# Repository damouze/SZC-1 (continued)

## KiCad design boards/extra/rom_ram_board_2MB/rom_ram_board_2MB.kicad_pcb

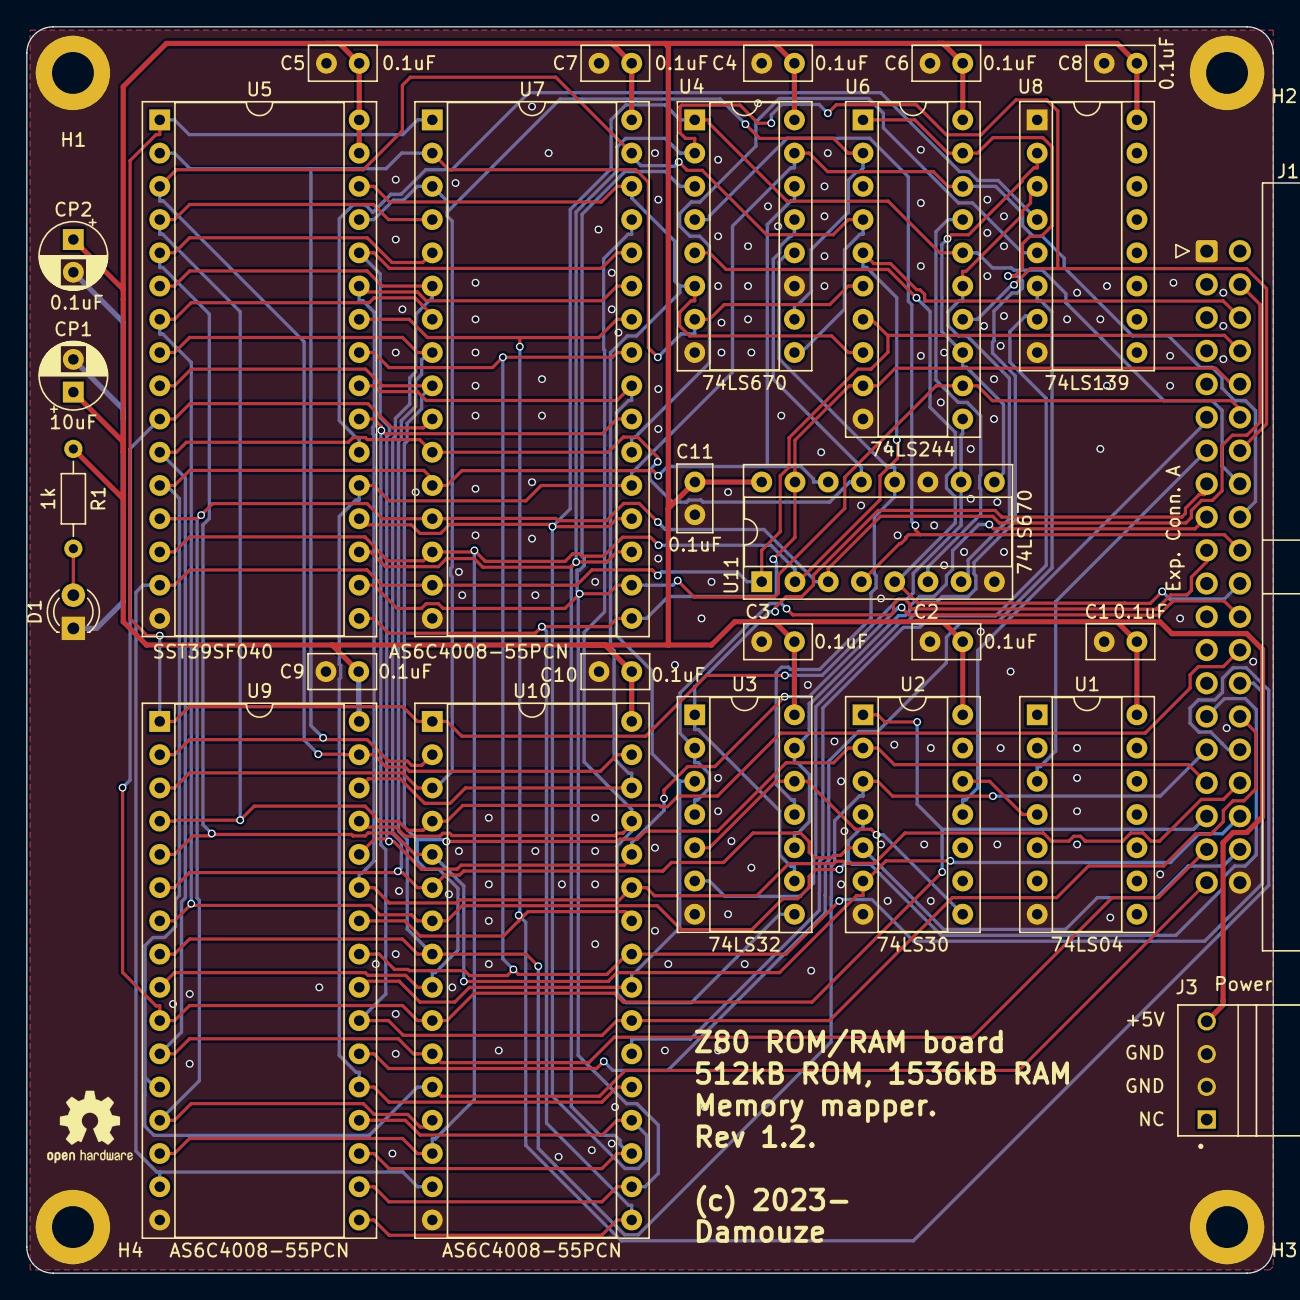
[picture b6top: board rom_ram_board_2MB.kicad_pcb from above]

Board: 2 copper layers, 95.2 x 95.2 mm, 32 parts (0 on the bottom side), 50 nets.

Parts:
C1, C2, C3, C4, C5, C6, C7, C8, C9, C10, C11: 0.1uF; C_Disc_D5.0mm_W2.5mm_P2.50mm
CP1: 10uF; CP_Radial_D5.0mm_P2.50mm
CP2: 0.1uF; CP_Radial_D5.0mm_P2.50mm
D1: PWR_LED; LED_D3.0mm
H1, H2, H3, H4: MountingHole_Pad; MountingHole_3.2mm_M3_ISO7380_Pad
J1: Exp. Conn. A; IDC-Header_2x20_P2.54mm_Horizontal
J3: Power; TE_171826-4
R1: 1k; R_Axial_DIN0204_L3.6mm_D1.6mm_P7.62mm_Horizontal
U1: 74LS04; DIP-14_W7.62mm_Socket
U2: 74LS30; DIP-14_W7.62mm_Socket
U3: 74LS32; DIP-14_W7.62mm_Socket
U4, U11: 74LS670; DIP-16_W7.62mm_Socket
U5: SST39SF040; DIP-32_W15.24mm_Socket
U6: 74LS244; DIP-20_W7.62mm_Socket
U7, U9, U10: AS6C4008-55PCN; DIP-32_W15.24mm_Socket
U8: 74LS139; DIP-16_W7.62mm_Socket

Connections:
/+5V: C1.1, C2.1, C3.1, C4.1, C5.1, C6.1, C7.1, C8.1, C9.1, C10.1, C11.1, CP1.1, CP2.1, J3.4, R1.1, U1.14 (VCC), U2.14 (VCC), U3.14 (VCC), U4.16 (VCC), U5.31 (PGM), U5.32 (VCC), U6.20 (VCC), U7.32 (VCC), U8.16 (VCC), U9.32 (VCC), U10.32 (VCC), U11.16 (VCC)
/B_A0: J1.39, U4.14 (Wa), U5.12 (A0), U7.12 (A0), U9.12 (A0), U10.12 (A0), U11.14 (Wa)
/B_A1: J1.37, U4.13 (Wb), U5.11 (A1), U7.11 (A1), U9.11 (A1), U10.11 (A1), U11.13 (Wb)
/B_A2: J1.35, U2.1, U5.10 (A2), U7.10 (A2), U9.10 (A2), U10.10 (A2)
/B_A3: J1.33, U2.2, U5.9 (A3), U7.9 (A3), U9.9 (A3), U10.9 (A3)
/B_A4: J1.31, U2.3, U5.8 (A4), U7.8 (A4), U9.8 (A4), U10.8 (A4)
/B_A5: J1.29, U2.4, U5.7 (A5), U7.7 (A5), U9.7 (A5), U10.7 (A5)
/B_A6: J1.38, U2.5, U5.6 (A6), U7.6 (A6), U9.6 (A6), U10.6 (A6)
/B_A7: J1.36, U2.6, U5.5 (A7), U7.5 (A7), U9.5 (A7), U10.5 (A7)
/B_A8: J1.34, U5.27 (A8), U7.27 (A8), U9.27 (A8), U10.27 (A8)
/B_A9: J1.32, U5.26 (A9), U7.26 (A9), U9.26 (A9), U10.26 (A9)
/B_A10: J1.30, U5.23 (A10), U7.23 (A10), U9.23 (A10), U10.23 (A10)
/B_A11: J1.28, U5.25 (A11), U7.25 (A11), U9.25 (A11), U10.25 (A11)
/B_A12: J1.26, U5.4 (A12), U7.4 (A12), U9.4 (A12), U10.4 (A12)
/B_A13: J1.24, U5.28 (A13), U7.28 (A13), U9.28 (A13), U10.28 (A13)
/B_A14: J1.22, U4.5 (Ra), U11.5 (Ra)
/B_A15: J1.20, U4.4 (Rb), U11.4 (Rb)
/B_D0: J1.18, U4.15 (D1), U5.21 (D7), U6.18 (O0a), U7.21 (DQ7), U9.21 (DQ7), U10.21 (DQ7)
/B_D1: J1.16, U4.1 (D2), U5.20 (D6), U6.16 (O1a), U7.20 (DQ6), U9.20 (DQ6), U10.20 (DQ6)
/B_D2: J1.14, U4.2 (D3), U5.19 (D5), U6.14 (O2a), U7.19 (DQ5), U9.19 (DQ5), U10.19 (DQ5)
/B_D3: J1.12, U4.3 (D4), U5.18 (D4), U6.12 (O3a), U7.18 (DQ4), U9.18 (DQ4), U10.18 (DQ4)
/B_D4: J1.10, U5.17 (D3), U6.9 (O0b), U7.17 (DQ3), U9.17 (DQ3), U10.17 (DQ3), U11.15 (D1)
/B_D5: J1.8, U5.15 (D2), U6.7 (O1b), U7.15 (DQ2), U9.15 (DQ2), U10.15 (DQ2), U11.1 (D2)
/B_D6: J1.6, U5.14 (D1), U6.5 (O2b), U7.14 (DQ1), U9.14 (DQ1), U10.14 (DQ1), U11.2 (D3)
/B_D7: J1.4, U5.13 (D0), U7.13 (DQ0), U9.13 (DQ0), U10.13 (DQ0), U11.3 (D4)
/GND: C1.2, C2.2, C3.2, C4.2, C5.2, C6.2, C7.2, C8.2, C9.2, C10.2, C11.2, CP1.2, CP2.2, D1.1 (K), H1.1, H2.1, H3.1, H4.1, J1.1, J1.40, J3.2, J3.3, U1.7 (GND), U2.7 (GND), U3.7 (GND), U4.8 (GND), U4.11 (~Er), U5.16 (GND), U6.10 (GND), U7.16 (VSS), U8.1 (E), U8.8 (GND), U9.16 (VSS), U10.16 (VSS), U11.8 (GND), U11.11 (~Er)
/IORQ: U1.4, U2.12
/R_A14: U4.10 (Q1), U5.29 (A14), U6.2 (I0a), U7.3 (A14), U9.3 (A14), U10.3 (A14)
/R_A15: U4.9 (Q2), U5.3 (A15), U6.4 (I1a), U7.31 (A15), U9.31 (A15), U10.31 (A15)
/R_A16: U4.7 (Q3), U5.2 (A16), U6.6 (I2a), U7.2 (A16), U9.2 (A16), U10.2 (A16)
/R_A17: U4.6 (Q4), U5.30 (A17), U6.8 (I3a), U7.30 (A17), U9.30 (A17), U10.30 (A17)
/R_A18: U5.1 (A18), U6.11 (I0b), U7.1 (A18), U9.1 (A18), U10.1 (A18), U11.10 (Q1)
/R_A19: U6.13 (I1b), U8.2 (A0), U11.9 (Q2)
/R_A20: U6.15 (I2b), U8.3 (A1), U11.7 (Q3)
/R_A21: U6.17 (I3b), U11.6 (Q4)
/~B_IORQ: J1.13, U1.3
/~B_M1: J1.11, U2.11
/~B_MREQ: J1.15, U3.1, U3.9
/~B_RD: J1.19, U3.2, U3.4
/~B_WR: J1.17, U3.10, U3.13
/~IO_RD: U3.6, U6.1 (OEa), U6.19 (OEb)
/~IO_WR: U3.11, U4.12 (~Ew), U11.12 (~Ew)
/~MM_RD: U3.3, U5.24 (OE), U7.24 (OE#), U9.24 (OE#), U10.24 (OE#)
/~MM_WR: U3.8, U7.29 (WE#), U9.29 (WE#), U10.29 (WE#)
/~RAM1_CS: U7.22 (CE#), U8.5 (O1)
/~RAM2_CS: U8.6 (O2), U9.22 (CE#)
/~RAM3_CS: U8.7 (O3), U10.22 (CE#)
/~ROM_CS: U5.22 (CE), U8.4 (O0)
unnamed: D1.2 (A), R1.2
unnamed: U2.8, U3.5, U3.12

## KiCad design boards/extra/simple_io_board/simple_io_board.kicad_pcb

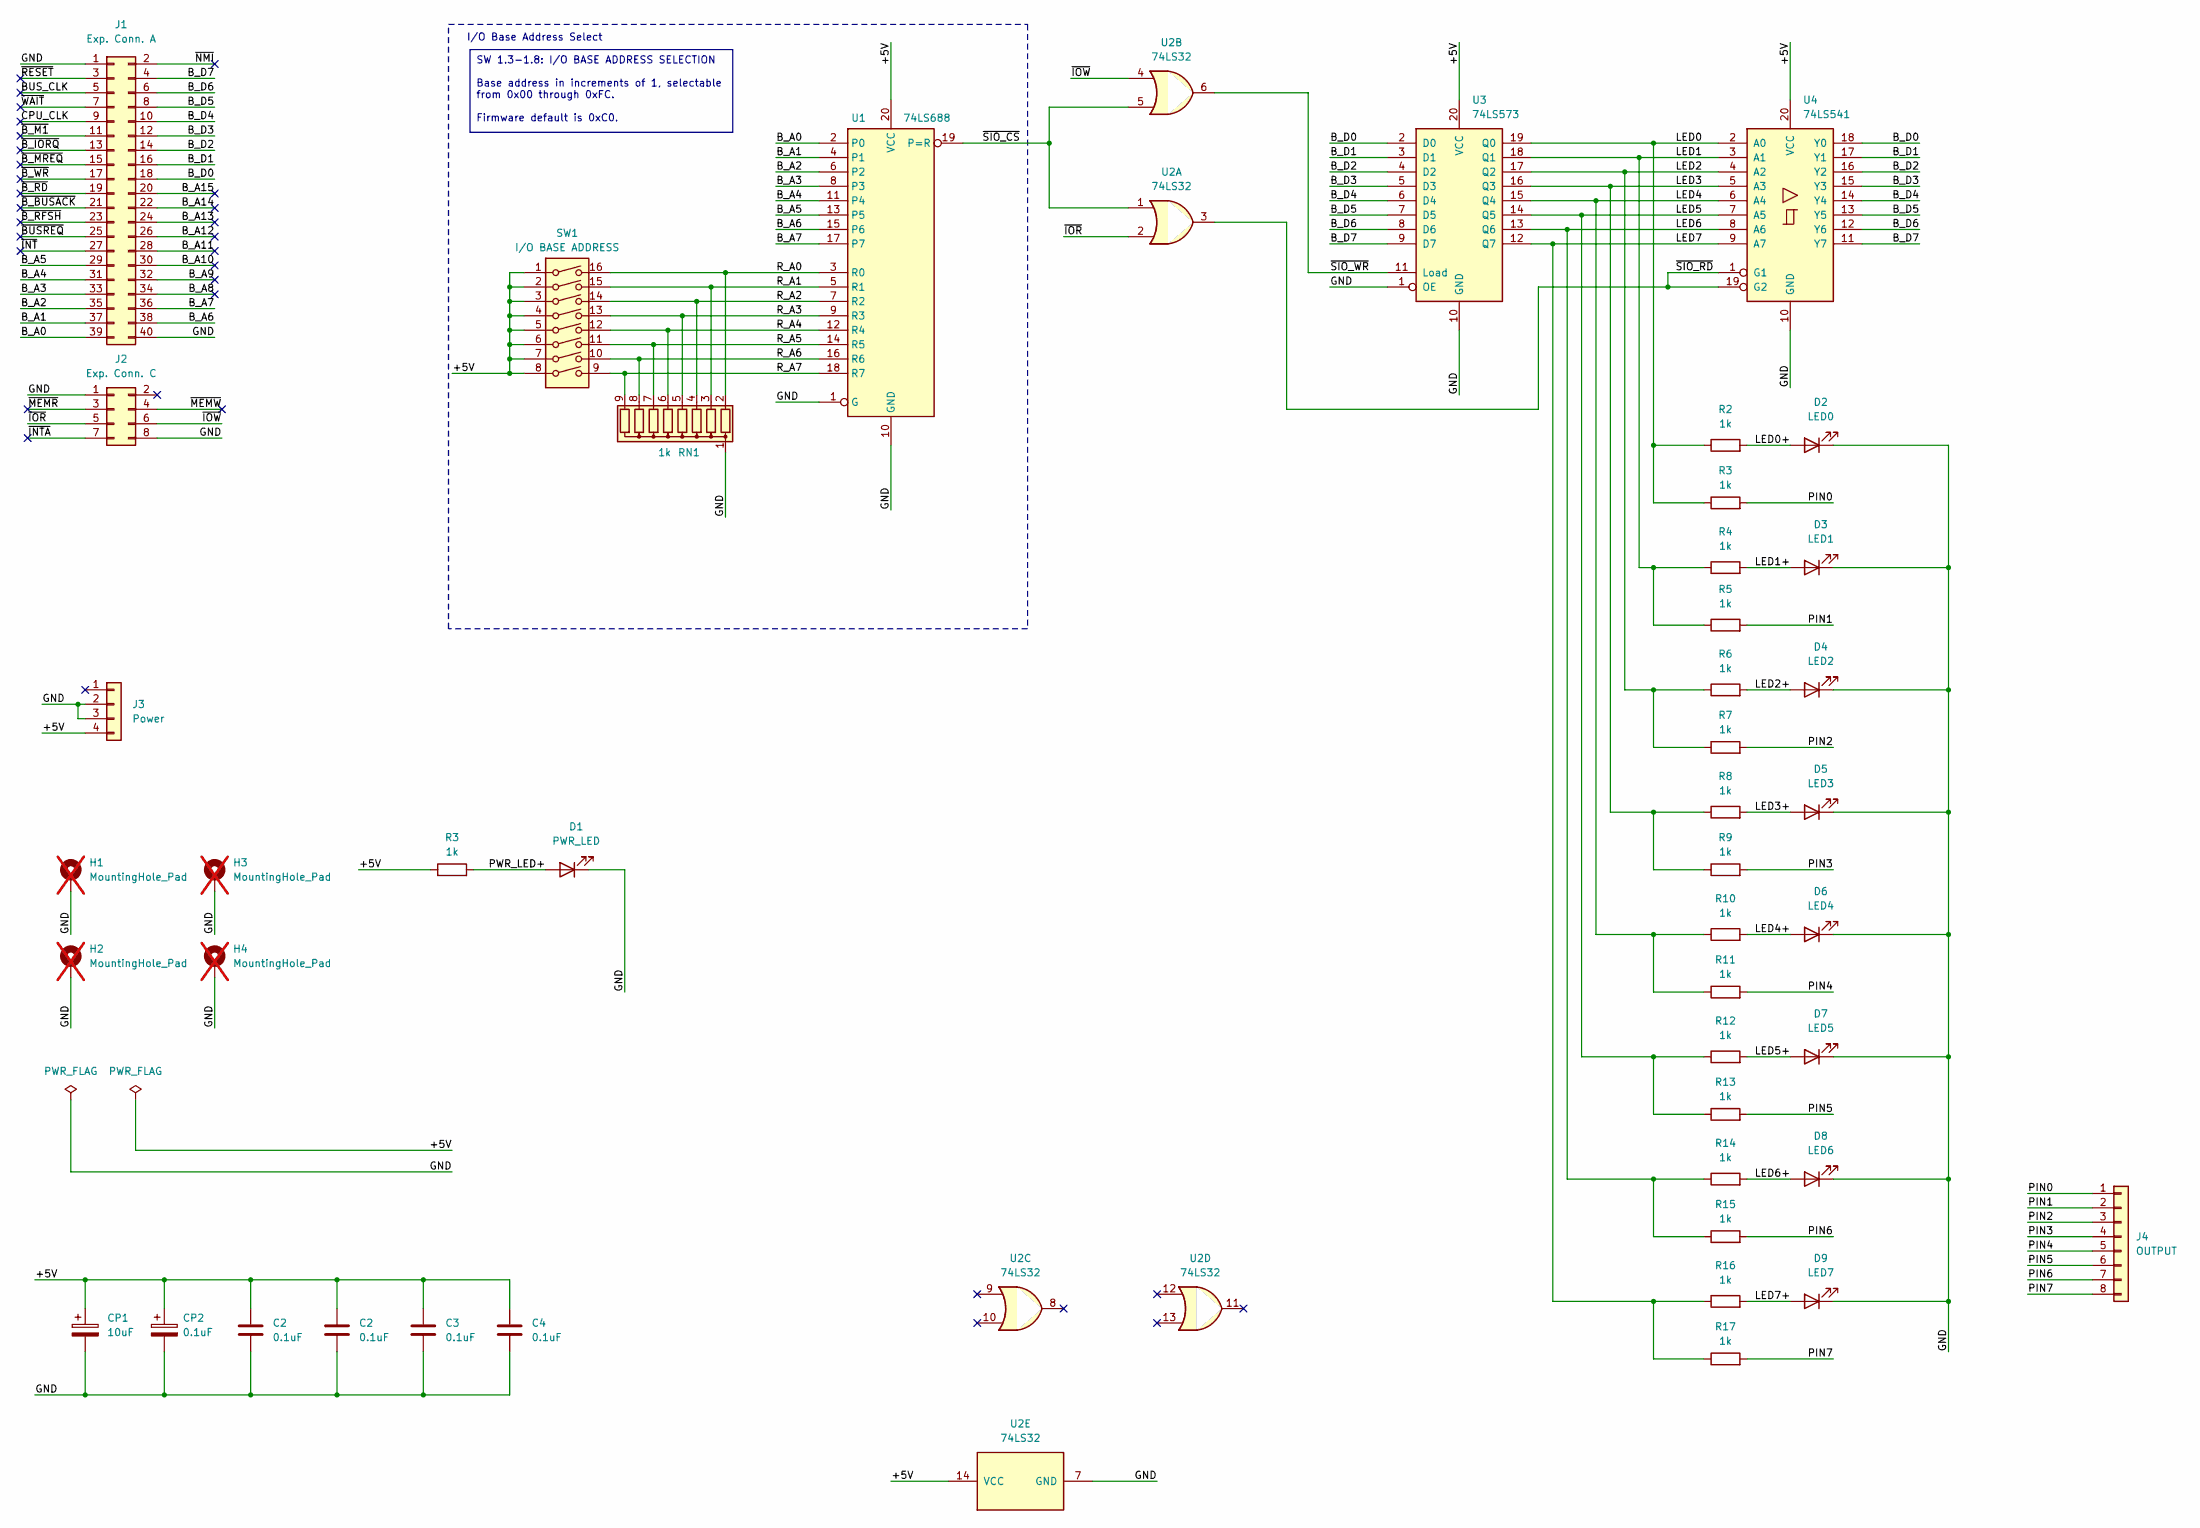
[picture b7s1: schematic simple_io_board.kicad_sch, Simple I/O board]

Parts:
C2, C3, C4: 0.1uF; C_Disc_D5.0mm_W2.5mm_P2.50mm; MPN FG28X7R1H104KNT06
CP1: 10uF; CP_Radial_D5.0mm_P2.50mm; MPN ECA1HM100I
CP2: 0.1uF; CP_Radial_D5.0mm_P2.50mm; MPN KS104M050C07RR0VH2FP0
D1: PWR_LED; LED_D3.0mm; MPN HLMP-1700
D2: LED0; LED_D3.0mm; MPN HLMP-1700
D3: LED1; LED_D3.0mm; MPN HLMP-1700
D4: LED2; LED_D3.0mm; MPN HLMP-1700
D5: LED3; LED_D3.0mm; MPN HLMP-1700
D6: LED4; LED_D3.0mm; MPN HLMP-1700
D7: LED5; LED_D3.0mm; MPN HLMP-1700
D8: LED6; LED_D3.0mm; MPN HLMP-1700
D9: LED7; LED_D3.0mm; MPN HLMP-1700
H1, H2, H3, H4: MountingHole_Pad; MountingHole_3.2mm_M3_ISO7380_Pad; not fitted
J1: Exp. Conn. A; IDC-Header_2x20_P2.54mm_Horizontal; MPN X9555WR-2x20-6TV01
J2: Exp. Conn. C; IDC-Header_2x04_P2.54mm_Horizontal; MPN 75867-132LF
J3: Power; TE_171826-4; MPN 171826-4
J4: OUTPUT; PinHeader_1x08_P2.54mm_Horizontal; MPN PZ254R-11-08P
R2, R3, R4, R5, R6, R7, R8, R9, R10, R11, R12, R13, R14, R15, R16, R17: 1k; R_Axial_DIN0204_L3.6mm_D1.6mm_P7.62mm_Horizontal; MPN MBA02040C1001FC100
RN1: 1k; R_Array_SIP9; MPN MBA02040C1001FC100
SW1: I/O BASE ADDRESS; SW_DIP_SPSTx08_Slide_6.7x21.88mm_W7.62mm_P2.54mm_LowProfile; MPN DS-08BLP
U1: 74LS688; DIP-20_W7.62mm_Socket; MPN 1-2199298-6
U2: 74LS32; DIP-14_W7.62mm_Socket; MPN 1-2199298-3
U3: 74LS573; DIP-20_W7.62mm_Socket; MPN 1-2199298-6
U4: 74LS541; DIP-20_W7.62mm_Socket; MPN 1-2199298-6

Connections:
/BUS_CLK: J1.5
/B_A0: J1.39, U1.2 (P0)
/B_A1: J1.37, U1.4 (P1)
/B_A2: J1.35, U1.6 (P2)
/B_A3: J1.33, U1.8 (P3)
/B_A4: J1.31, U1.11 (P4)
/B_A5: J1.29, U1.13 (P5)
/B_A6: J1.38, U1.15 (P6)
/B_A7: J1.36, U1.17 (P7)
/B_A8: J1.34
/B_A9: J1.32
/B_A10: J1.30
/B_A11: J1.28
/B_A12: J1.26
/B_A13: J1.24
/B_A14: J1.22
/B_A15: J1.20
/B_D0: J1.18, U3.2 (D0), U4.18 (Y0)
/B_D1: J1.16, U3.3 (D1), U4.17 (Y1)
/B_D2: J1.14, U3.4 (D2), U4.16 (Y2)
/B_D3: J1.12, U3.5 (D3), U4.15 (Y3)
/B_D4: J1.10, U3.6 (D4), U4.14 (Y4)
/B_D5: J1.8, U3.7 (D5), U4.13 (Y5)
/B_D6: J1.6, U3.8 (D6), U4.12 (Y6)
/B_D7: J1.4, U3.9 (D7), U4.11 (Y7)
/CPU_CLK: J1.9
/GND: C2.2, C3.2, C4.2, CP1.2, CP2.2, D1.1 (K), D2.1 (K), D3.1 (K), D4.1 (K), D5.1 (K), D6.1 (K), D7.1 (K), D8.1 (K), D9.1 (K), H1.1, H2.1, H3.1, H4.1, J1.1, J1.40, J2.1, J2.8, J3.2, J3.3, RN1.1 (common), U1.1 (G), U1.10 (GND), U2.7 (GND), U3.1 (OE), U3.10 (GND), U4.10 (GND); also elsewhere on the board
/LED0+: D2.2 (A), R2.2
/LED1: R4.1, R5.1, U3.18 (Q1), U4.3 (A1)
/LED1+: D3.2 (A), R4.2
/LED2: R6.1, R7.1, U3.17 (Q2), U4.4 (A2)
/LED2+: D4.2 (A), R6.2
/LED3: R8.1, R9.1, U3.16 (Q3), U4.5 (A3)
/LED3+: D5.2 (A), R8.2
/LED4: R10.1, R11.1, U3.15 (Q4), U4.6 (A4)
/LED4+: D6.2 (A), R10.2
/LED5: R12.1, R13.1, U3.14 (Q5), U4.7 (A5)
/LED5+: D7.2 (A), R12.2
/LED6: R14.1, R15.1, U3.13 (Q6), U4.8 (A6)
/LED6+: D8.2 (A), R14.2
/LED7: R16.1, R17.1, U3.12 (Q7), U4.9 (A7)
/LED7+: D9.2 (A), R16.2
/PIN1: J4.2, R5.2
/PIN2: J4.3, R7.2
/PIN3: J4.4, R9.2
/PIN4: J4.5, R11.2
/PIN5: J4.6, R13.2
/PIN6: J4.7, R15.2
/PIN7: J4.8, R17.2
/R_A0: RN1.2 (R1), SW1.16, U1.3 (R0)
/R_A1: RN1.3 (R2), SW1.15, U1.5 (R1)
/R_A2: RN1.4 (R3), SW1.14, U1.7 (R2)
/R_A3: RN1.5 (R4), SW1.13, U1.9 (R3)
/R_A4: RN1.6 (R5), SW1.12, U1.12 (R4)
/R_A5: RN1.7 (R6), SW1.11, U1.14 (R5)
/R_A6: RN1.8 (R7), SW1.10, U1.16 (R6)
/R_A7: RN1.9 (R8), SW1.9, U1.18 (R7)
/~BUSREQ: J1.25
/~B_BUSACK: J1.21
/~B_IORQ: J1.13
/~B_M1: J1.11
/~B_MREQ: J1.15
/~B_RD: J1.19
/~B_RFSH: J1.23
/~B_WR: J1.17
/~INTA: J2.7
/~INT: J1.27
/~IOR: J2.5, U2.2
/~IOW: J2.6, U2.4
/~MEMR: J2.3
/~MEMW: J2.4
/~NMI: J1.2
/~RESET: J1.3
/~SIO_CS: U1.19 (P=R), U2.1, U2.5
/~SIO_RD: U2.3, U4.1 (G1), U4.19 (G2)
/~SIO_WR: U2.6, U3.11 (Load)
/~WAIT: J1.7

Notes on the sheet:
SW 1.3-1.8: I/O BASE ADDRESS SELECTION Base address in increments of 1, selectable from 0x00 through 0xFC. Firmware default is 0xC0.
I/O Base Address Select

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
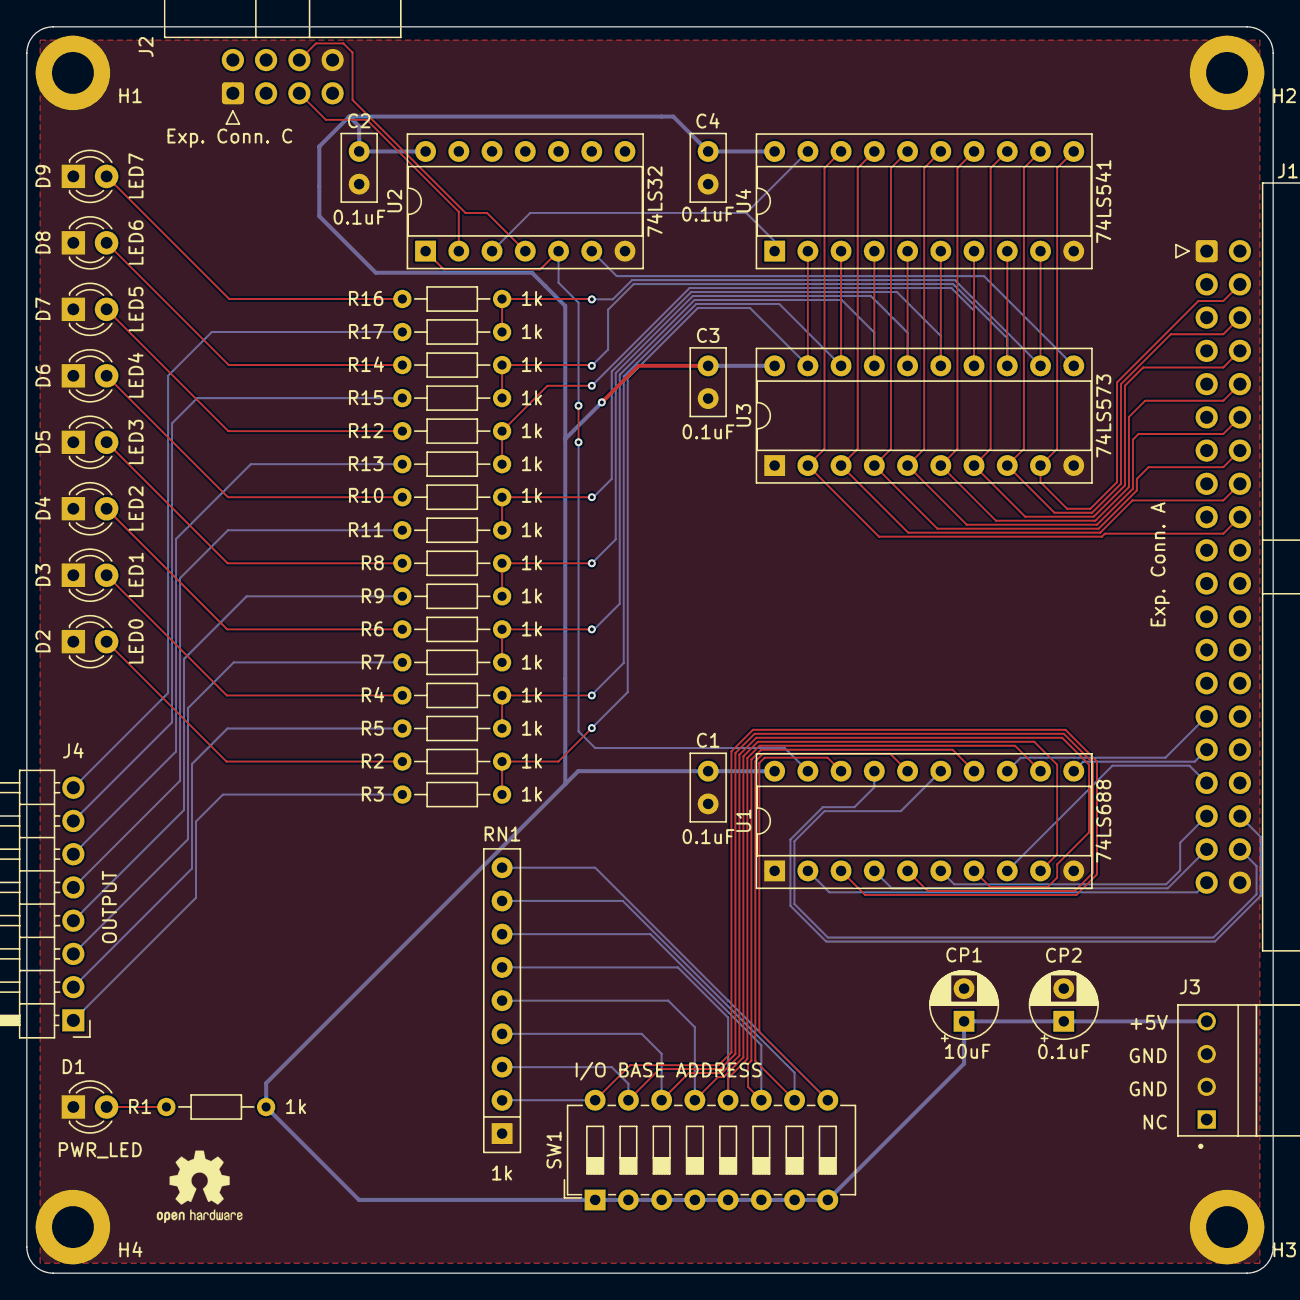
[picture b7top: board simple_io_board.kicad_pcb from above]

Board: 2 copper layers, 95.2 x 95.2 mm, 46 parts (0 on the bottom side), 56 nets.

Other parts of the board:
C1: 0.1uF; C_Disc_D5.0mm_W2.5mm_P2.50mm
R1: 1k; R_Axial_DIN0204_L3.6mm_D1.6mm_P7.62mm_Horizontal

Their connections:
/GND: C1.2; also elsewhere on the board
